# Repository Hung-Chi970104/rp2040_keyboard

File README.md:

# Full-size keyboard with integrated RP2040 chip
A keyboard that’s actually a computer! Inspired by from Raspberry Pi 500, but instead with a powerful RP2040 inside, you can code as you type, like run Python, compile C/C++, and literally type programs on the go!

## Components
- RP2040
- 12MHz Crystal (ABM8-272-T3)
- 2MB Flash Storage (W25Q16JVUXIQ)
- Buck-Boost Switching Regulator (RT6154AGQW)
- USB-C (TYPE-C-31-M-12)

## Designs

## Conclusion
I gotta be honest working on this wasn't as easy as I thought, mainly beacuse of new layout for RP2040 and my poor planning (yeah that's my problem).......But anyways I'll order this right after I get my RP2040 devboard that I built previously just in case I made some stupid mistakes lol

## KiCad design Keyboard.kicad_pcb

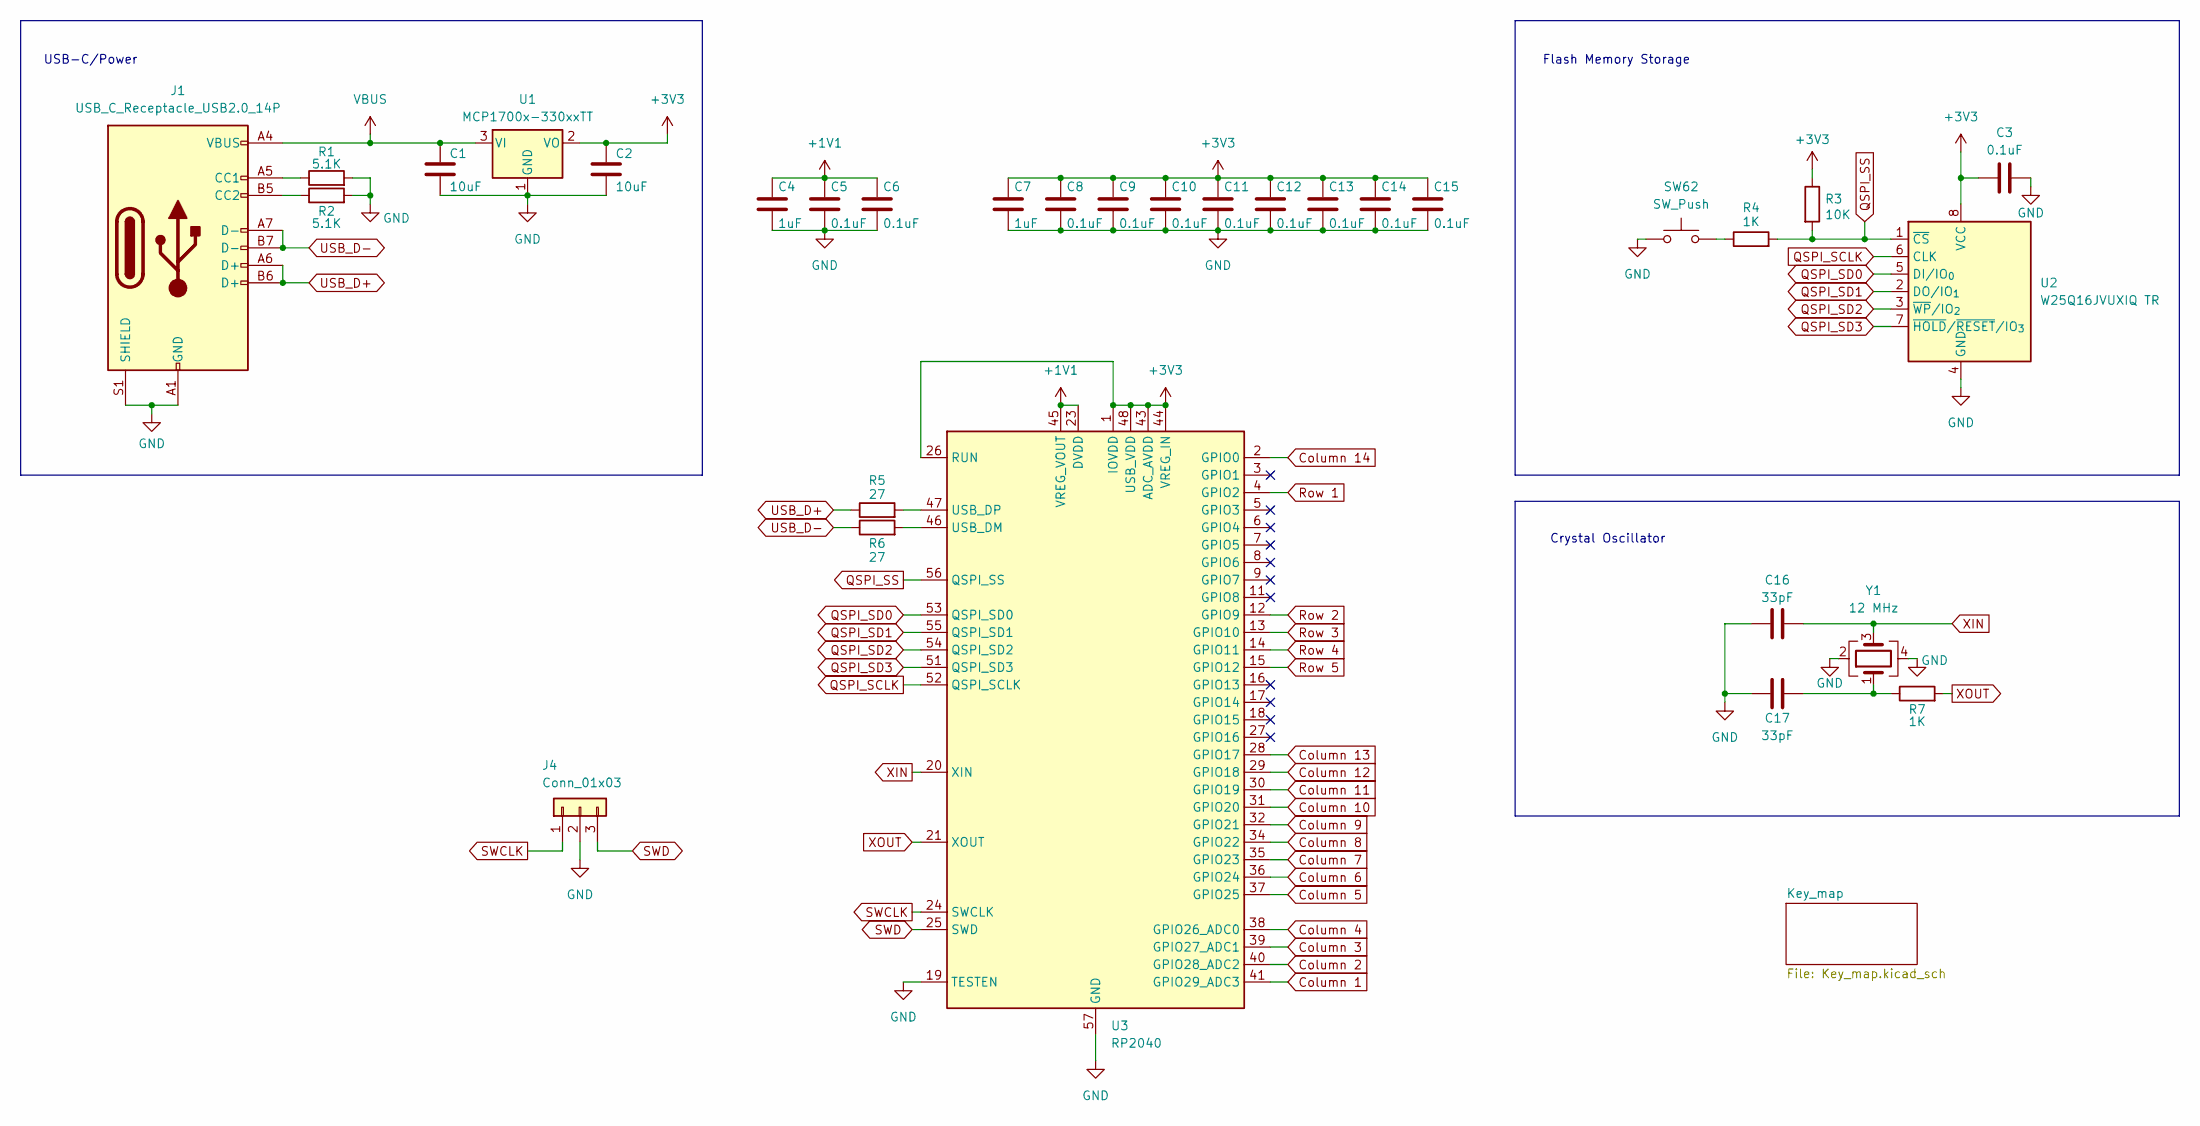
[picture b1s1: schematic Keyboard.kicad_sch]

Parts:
C1, C2: 10uF; C_0603_1608Metric
C3, C5, C6, C8, C9, C10, C11, C12, C13, C14, C15: 0.1uF; C_0402_1005Metric
C4, C7: 1uF; C_0402_1005Metric
C16, C17: 33pF; C_0402_1005Metric
J1: USB_C_Receptacle_USB2.0_14P; USB_C_Receptacle_HRO_TYPE-C-31-M-12
J4: Conn_01x03; PinHeader_1x03_P2.54mm_Vertical
R1, R2: 5.1K; R_0402_1005Metric
R3: 10K; R_0402_1005Metric
R4, R7: 1K; R_0402_1005Metric
R5, R6: 27; R_0402_1005Metric
SW62: SW_Push; SW_Push_SPST_NO_Alps_SKRK
U1: MCP1700x-330xxTT; SOT-23
U2: W25Q16JVUXIQ TR; Winbond_USON-8-1EP_3x2mm_P0.5mm_EP0.2x1.6mm
U3: RP2040; QFN-56-1EP_7x7mm_P0.4mm_EP3.2x3.2mm
Y1: 12 MHz; Crystal_SMD_3225-4Pin_3.2x2.5mm

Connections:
+1V1: C4.1, C5.1, C6.1, U3.23 (DVDD), U3.45 (VREG_VOUT), U3.50 (DVDD)
+3V3: C2.1, C3.1, C7.1, C8.1, C9.1, C10.1, C11.1, C12.1, C13.1, C14.1, C15.1, R3.1, U1.2 (VO), U2.8 (VCC), U3.1 (IOVDD), U3.10 (IOVDD), U3.22 (IOVDD), U3.26 (RUN), U3.33 (IOVDD), U3.42 (IOVDD), U3.43 (ADC_AVDD), U3.44 (VREG_IN), U3.48 (USB_VDD), U3.49 (IOVDD)
Column 1: U3.41 (GPIO29_ADC3); also elsewhere on the board
Column 2: U3.40 (GPIO28_ADC2); also elsewhere on the board
Column 3: U3.39 (GPIO27_ADC1); also elsewhere on the board
Column 4: U3.38 (GPIO26_ADC0); also elsewhere on the board
Column 5: U3.37 (GPIO25); also elsewhere on the board
Column 6: U3.36 (GPIO24); also elsewhere on the board
Column 7: U3.35 (GPIO23); also elsewhere on the board
Column 8: U3.34 (GPIO22); also elsewhere on the board
Column 9: U3.32 (GPIO21); also elsewhere on the board
Column 10: U3.31 (GPIO20); also elsewhere on the board
Column 11: U3.30 (GPIO19); also elsewhere on the board
Column 12: U3.29 (GPIO18); also elsewhere on the board
Column 13: U3.28 (GPIO17); also elsewhere on the board
Column 14: U3.2 (GPIO0); also elsewhere on the board
GND: C1.2, C2.2, C3.2, C4.2, C5.2, C6.2, C7.2, C8.2, C9.2, C10.2, C11.2, C12.2, C13.2, C14.2, C15.2, C16.1, C17.1, J1.A1 (GND), J1.A12 (GND), J1.B1 (GND), J1.B12 (GND), J1.S1 (SHIELD), J4.2, R1.2, R2.2, SW62.1, U1.1 (GND), U2.4 (GND), U3.19 (TESTEN), U3.57 (GND), Y1.2, Y1.4
unnamed: C17.2, R7.1, Y1.1
unnamed: J1.A5 (CC1), R1.1
unnamed: J1.B5 (CC2), R2.1
unnamed: R4.1, SW62.2
unnamed: R6.2, U3.46 (USB_DM)
unnamed: R5.2, U3.47 (USB_DP)
QSPI_SCLK: U2.6 (CLK), U3.52 (QSPI_SCLK)
QSPI_SD0: U2.5 (DI/IO_{0}), U3.53 (QSPI_SD0)
QSPI_SD1: U2.2 (DO/IO_{1}), U3.55 (QSPI_SD1)
QSPI_SD2: U2.3 (~WP/IO_{2}), U3.54 (QSPI_SD2)
QSPI_SD3: U2.7 (~HOLD/~RESET/IO_{3}), U3.51 (QSPI_SD3)
QSPI_SS: R3.2, R4.2, U2.1 (~CS), U3.56 (QSPI_SS)
Row 1: U3.4 (GPIO2); also elsewhere on the board
Row 2: U3.12 (GPIO9); also elsewhere on the board
Row 3: U3.13 (GPIO10); also elsewhere on the board
Row 4: U3.14 (GPIO11); also elsewhere on the board
Row 5: U3.15 (GPIO12); also elsewhere on the board
SWCLK: J4.1, U3.24 (SWCLK)
SWD: J4.3, U3.25 (SWD)
USB_D+: J1.A6 (D+), J1.B6 (D+), R5.1
USB_D-: J1.A7 (D-), J1.B7 (D-), R6.1
VBUS: C1.1, J1.A4 (VBUS), J1.A9 (VBUS), J1.B4 (VBUS), J1.B9 (VBUS), U1.3 (VI)
XIN: C16.2, U3.20 (XIN), Y1.3
XOUT: R7.2, U3.21 (XOUT)

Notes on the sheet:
Crystal Oscillator
Flash Memory Storage
USB-C/Power

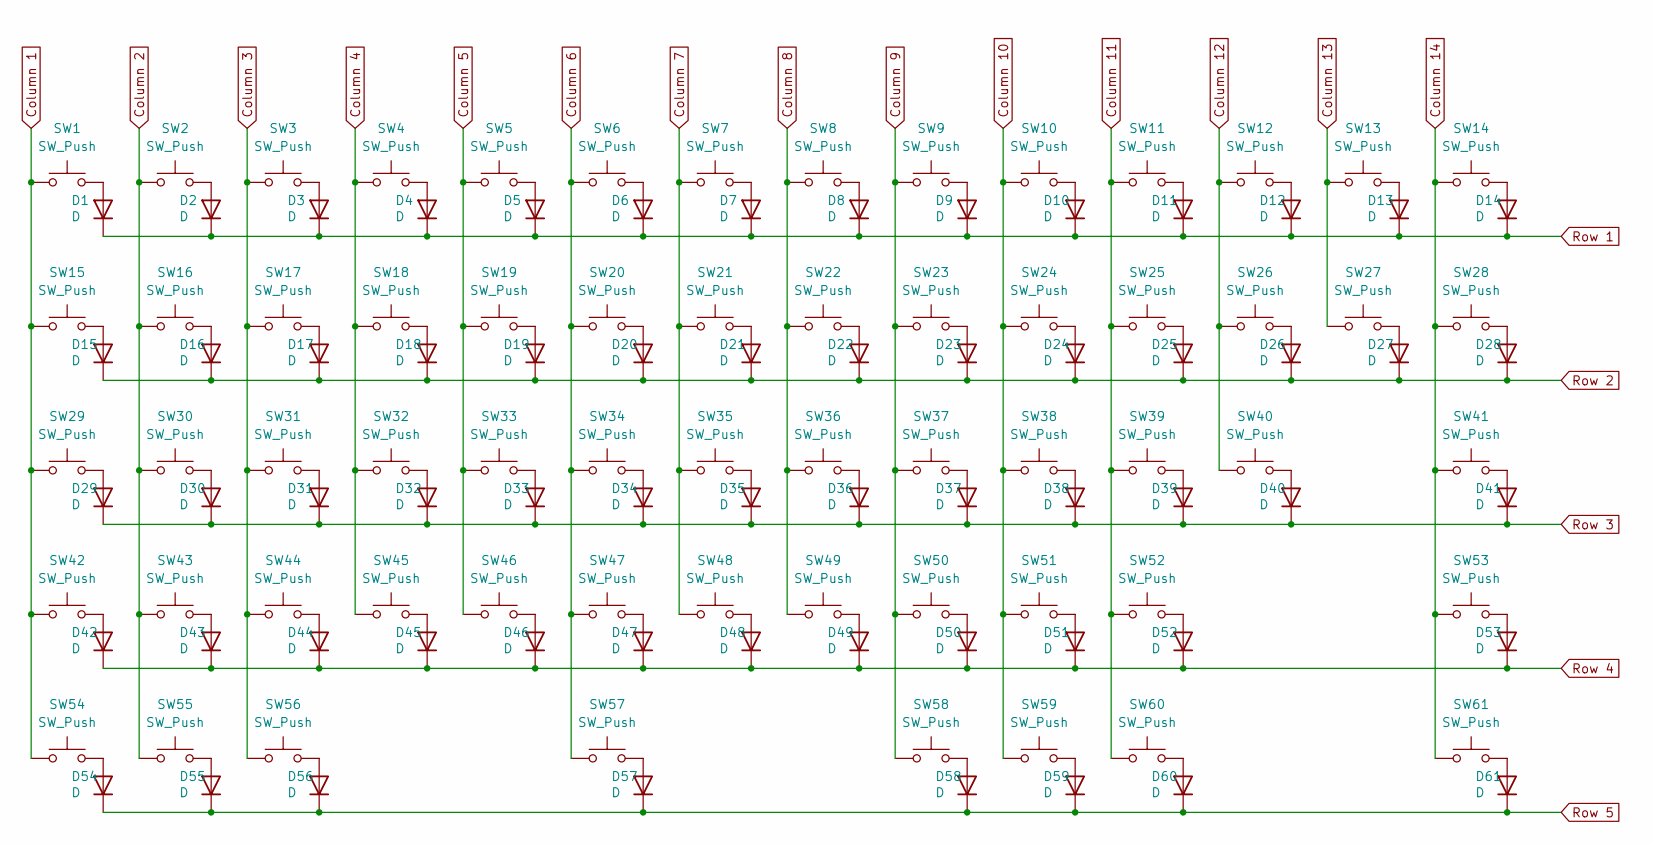
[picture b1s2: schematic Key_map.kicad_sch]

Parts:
D1, D2, D3, D4, D5, D6, D7, D8, D9, D10, D11, D12, D13, D14, D15, D16, D17, D18, D19, D20, D21, D22, D23, D24, D25, D26, D27, D28, D29, D30, D31, D32, D33, D34, D35, D36, D37, D38, D39, D40, D41, D42, D43, D44, D45, D46, D47, D48, D49, D50, D51, D52, D53, D54, D55, D56, D57, D58, D59, D60, D61: D; D_0402_1005Metric
SW1, SW2, SW3, SW4, SW5, SW6, SW7, SW8, SW9, SW10, SW11, SW12, SW13, SW16, SW17, SW18, SW19, SW20, SW21, SW22, SW23, SW24, SW25, SW26, SW27, SW30, SW31, SW32, SW33, SW34, SW35, SW36, SW37, SW38, SW39, SW40, SW43, SW44, SW45, SW46, SW47, SW48, SW49, SW50, SW51, SW52: SW_Push; SW_Cherry_MX_PCB_1.00u
SW14: SW_Push; SW_Cherry_MX_PCB_2.00u
SW15, SW28: SW_Push; SW_Cherry_MX_PCB_1.50u
SW29: SW_Push; SW_Cherry_MX_PCB_1.75u
SW41, SW42: SW_Push; SW_Cherry_MX_PCB_2.25u
SW53: SW_Push; SW_Cherry_MX_PCB_2.75u
SW54, SW55, SW56, SW58, SW59, SW60, SW61: SW_Push; SW_Cherry_MX_PCB_1.25u
SW57: SW_Push; SW_Cherry_MX_PCB_6.25u

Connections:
Column 1: SW1.1, SW15.1, SW29.1, SW42.1, SW54.1; also elsewhere on the board
Column 2: SW2.1, SW16.1, SW30.1, SW43.1, SW55.1; also elsewhere on the board
Column 3: SW3.1, SW17.1, SW31.1, SW44.1, SW56.1; also elsewhere on the board
Column 4: SW4.1, SW18.1, SW32.1, SW45.1; also elsewhere on the board
Column 5: SW5.1, SW19.1, SW33.1, SW46.1; also elsewhere on the board
Column 6: SW6.1, SW20.1, SW34.1, SW47.1, SW57.1; also elsewhere on the board
Column 7: SW7.1, SW21.1, SW35.1, SW48.1; also elsewhere on the board
Column 8: SW8.1, SW22.1, SW36.1, SW49.1; also elsewhere on the board
Column 9: SW9.1, SW23.1, SW37.1, SW50.1, SW58.1; also elsewhere on the board
Column 10: SW10.1, SW24.1, SW38.1, SW51.1, SW59.1; also elsewhere on the board
Column 11: SW11.1, SW25.1, SW39.1, SW52.1, SW60.1; also elsewhere on the board
Column 12: SW12.1, SW26.1, SW40.1; also elsewhere on the board
Column 13: SW13.1, SW27.1; also elsewhere on the board
Column 14: SW14.1, SW28.1, SW41.1, SW53.1, SW61.1; also elsewhere on the board
unnamed: D1.2 (A), SW1.2
unnamed: D2.2 (A), SW2.2
unnamed: D3.2 (A), SW3.2
unnamed: D4.2 (A), SW4.2
unnamed: D5.2 (A), SW5.2
unnamed: D6.2 (A), SW6.2
unnamed: D7.2 (A), SW7.2
unnamed: D8.2 (A), SW8.2
unnamed: D9.2 (A), SW9.2
unnamed: D10.2 (A), SW10.2
unnamed: D11.2 (A), SW11.2
unnamed: D12.2 (A), SW12.2
unnamed: D13.2 (A), SW13.2
unnamed: D14.2 (A), SW14.2
unnamed: D15.2 (A), SW15.2
unnamed: D16.2 (A), SW16.2
unnamed: D17.2 (A), SW17.2
unnamed: D18.2 (A), SW18.2
unnamed: D19.2 (A), SW19.2
unnamed: D20.2 (A), SW20.2
unnamed: D21.2 (A), SW21.2
unnamed: D22.2 (A), SW22.2
unnamed: D23.2 (A), SW23.2
unnamed: D24.2 (A), SW24.2
unnamed: D25.2 (A), SW25.2
unnamed: D26.2 (A), SW26.2
unnamed: D27.2 (A), SW27.2
unnamed: D28.2 (A), SW28.2
unnamed: D29.2 (A), SW29.2
unnamed: D30.2 (A), SW30.2
unnamed: D31.2 (A), SW31.2
unnamed: D32.2 (A), SW32.2
unnamed: D33.2 (A), SW33.2
unnamed: D34.2 (A), SW34.2
unnamed: D35.2 (A), SW35.2
unnamed: D36.2 (A), SW36.2
unnamed: D37.2 (A), SW37.2
unnamed: D38.2 (A), SW38.2
unnamed: D39.2 (A), SW39.2
unnamed: D40.2 (A), SW40.2
unnamed: D41.2 (A), SW41.2
unnamed: D42.2 (A), SW42.2
unnamed: D43.2 (A), SW43.2
unnamed: D44.2 (A), SW44.2
unnamed: D45.2 (A), SW45.2
unnamed: D46.2 (A), SW46.2
unnamed: D47.2 (A), SW47.2
unnamed: D48.2 (A), SW48.2
unnamed: D49.2 (A), SW49.2
unnamed: D50.2 (A), SW50.2
unnamed: D51.2 (A), SW51.2
unnamed: D52.2 (A), SW52.2
unnamed: D53.2 (A), SW53.2
unnamed: D54.2 (A), SW54.2
unnamed: D55.2 (A), SW55.2
unnamed: D56.2 (A), SW56.2
unnamed: D57.2 (A), SW57.2
unnamed: D58.2 (A), SW58.2
unnamed: D59.2 (A), SW59.2
unnamed: D60.2 (A), SW60.2
unnamed: D61.2 (A), SW61.2
Row 1: D1.1 (K), D2.1 (K), D3.1 (K), D4.1 (K), D5.1 (K), D6.1 (K), D7.1 (K), D8.1 (K), D9.1 (K), D10.1 (K), D11.1 (K), D12.1 (K), D13.1 (K), D14.1 (K); also elsewhere on the board
Row 2: D15.1 (K), D16.1 (K), D17.1 (K), D18.1 (K), D19.1 (K), D20.1 (K), D21.1 (K), D22.1 (K), D23.1 (K), D24.1 (K), D25.1 (K), D26.1 (K), D27.1 (K), D28.1 (K); also elsewhere on the board
Row 3: D29.1 (K), D30.1 (K), D31.1 (K), D32.1 (K), D33.1 (K), D34.1 (K), D35.1 (K), D36.1 (K), D37.1 (K), D38.1 (K), D39.1 (K), D40.1 (K), D41.1 (K); also elsewhere on the board
Row 4: D42.1 (K), D43.1 (K), D44.1 (K), D45.1 (K), D46.1 (K), D47.1 (K), D48.1 (K), D49.1 (K), D50.1 (K), D51.1 (K), D52.1 (K), D53.1 (K); also elsewhere on the board
Row 5: D54.1 (K), D55.1 (K), D56.1 (K), D57.1 (K), D58.1 (K), D59.1 (K), D60.1 (K), D61.1 (K); also elsewhere on the board

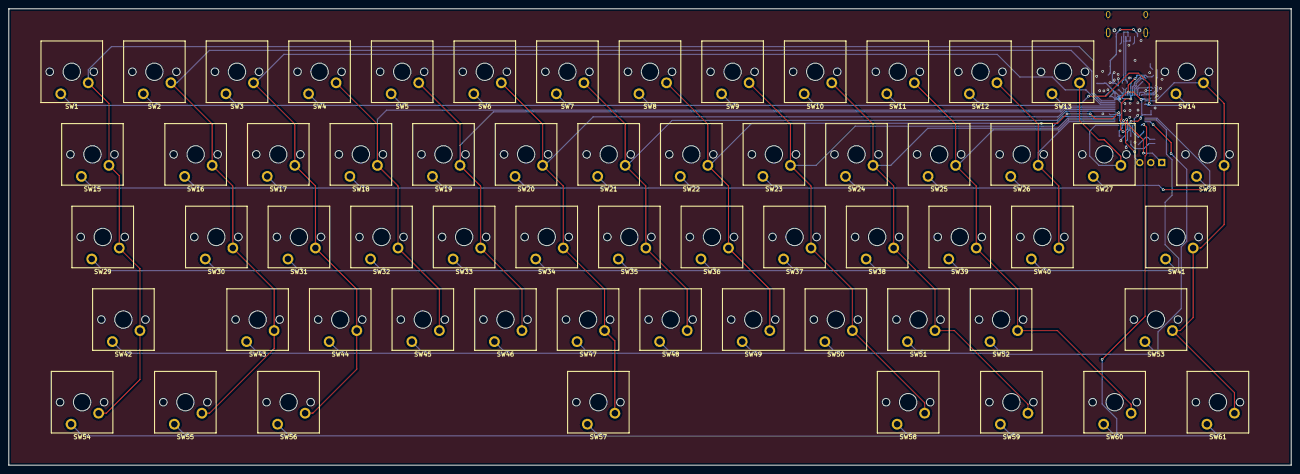
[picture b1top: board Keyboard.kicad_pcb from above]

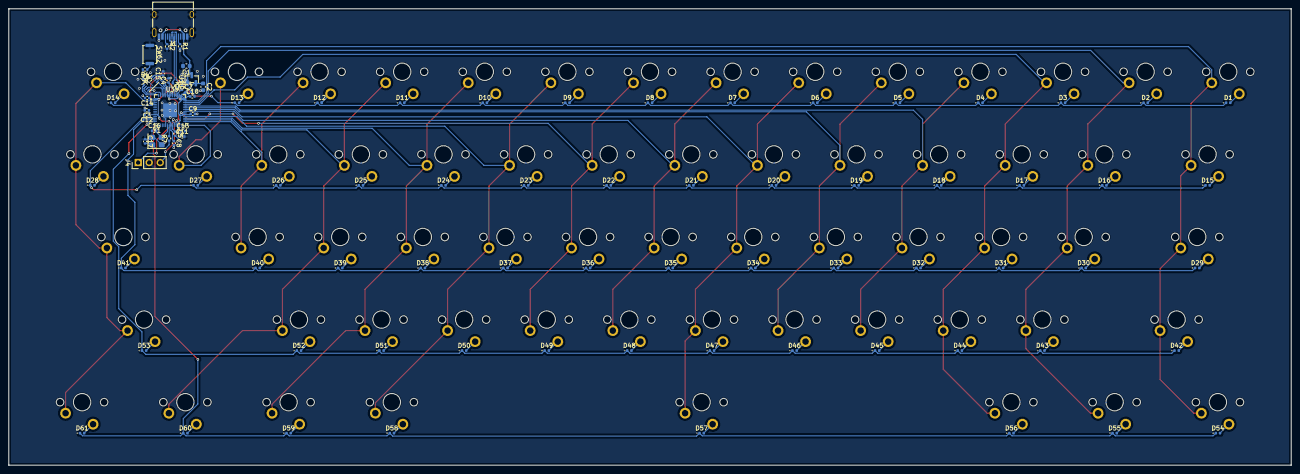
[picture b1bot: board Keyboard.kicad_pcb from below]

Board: 2 copper layers, 295.8 x 105.2 mm, 153 parts (92 on the bottom side), 102 nets.

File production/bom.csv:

Designator,Footprint,Quantity,Value,LCSC Part #
"C1, C2",0603,2,10uF,
"C10, C11, C12, C13, C14, C15, C3, C5, C6, C8, C9",0402,11,0.1uF,
"C16, C17",0402,2,33pF,
"C4, C7",0402,2,1uF,
"D1, D10, D11, D12, D13, D14, D15, D16, D17, D18, D19, D2, D20, D21, D22, D23, D24, D25, D26, D27, D28, D29, D3, D30, D31, D32, D33, D34, D35, D36, D37, D38, D39, D4, D40, D41, D42, D43, D44, D45, D46, D47, D48, D49, D5, D50, D51, D52, D53, D54, D55, D56, D57, D58, D59, D6, D60, D61, D7, D8, D9",0402,61,D,
J1,USB_C_Receptacle_HRO_TYPE-C-31-M-12,1,USB_C_Receptacle_USB2.0_14P,
J4,PinHeader_1x03_P2.54mm_Vertical,1,Conn_01x03,
"R1, R2",0402,2,5.1K,
R3,0402,1,10K,
"R4, R7",0402,2,1K,
"R5, R6",0402,2,27,
"SW1, SW10, SW11, SW12, SW13, SW16, SW17, SW18, SW19, SW2, SW20, SW21, SW22, SW23, SW24, SW25, SW26, SW27, SW3, SW30, SW31, SW32, SW33, SW34, SW35, SW36, SW37, SW38, SW39, SW4, SW40, SW43, SW44, SW45, SW46, SW47, SW48, SW49, SW5, SW50, SW51, SW52, SW6, SW7, SW8, SW9",SW_Cherry_MX_PCB_1.00u,46,SW_Push,
SW14,SW_Cherry_MX_PCB_2.00u,1,SW_Push,
"SW15, SW28",SW_Cherry_MX_PCB_1.50u,2,SW_Push,
SW29,SW_Cherry_MX_PCB_1.75u,1,SW_Push,
"SW41, SW42",SW_Cherry_MX_PCB_2.25u,2,SW_Push,
SW53,SW_Cherry_MX_PCB_2.75u,1,SW_Push,
"SW54, SW55, SW56, SW58, SW59, SW60, SW61",SW_Cherry_MX_PCB_1.25u,7,SW_Push,
SW57,SW_Cherry_MX_PCB_6.25u,1,SW_Push,
SW62,SW_Push_SPST_NO_Alps_SKRK,1,SW_Push,
U1,SOT-23,1,MCP1700x-330xxTT,
U2,Winbond_USON-8-1EP_3x2mm_P0.5mm_EP0.2x1.6mm,1,W25Q16JVUXIQ TR,
U3,QFN-56-1EP_7x7mm_P0.4mm_EP3.2x3.2mm,1,RP2040,
Y1,Crystal_SMD_3225-4Pin_3.2x2.5mm,1,12 MHz,

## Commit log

2025-12-28 Add README for full-size keyboard project
    Added project details for a full-size keyboard with RP2040 chip, including components, images, and a conclusion.
2025-12-28 Fix typo in Conclusion section
    Corrected a typo in the 'Conclusion' section of the README.
2025-12-30 Fixed DRC
2026-01-29 Update images because cdn is down
2026-01-29 Update images
2026-01-29 Fix image URLs
2026-01-29 Update image
2026-01-29 Remove duplicate image entry in README.md
    Removed duplicate image from the README.
2026-01-29 Change image link to GitHub URL
    Updated image link in README to point to GitHub.
2026-01-30 Refactor images in README.md
    Updated image links in the README and removed duplicates.
